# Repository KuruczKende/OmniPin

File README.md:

# OmniPin

## Description
This is a badge that can be customized while worn. The project contructs from a mobile application and a device.

### Technical Details
Microcontroller used: ESP32-C3-Mini-1
E-Paper: GDEM0154F51H

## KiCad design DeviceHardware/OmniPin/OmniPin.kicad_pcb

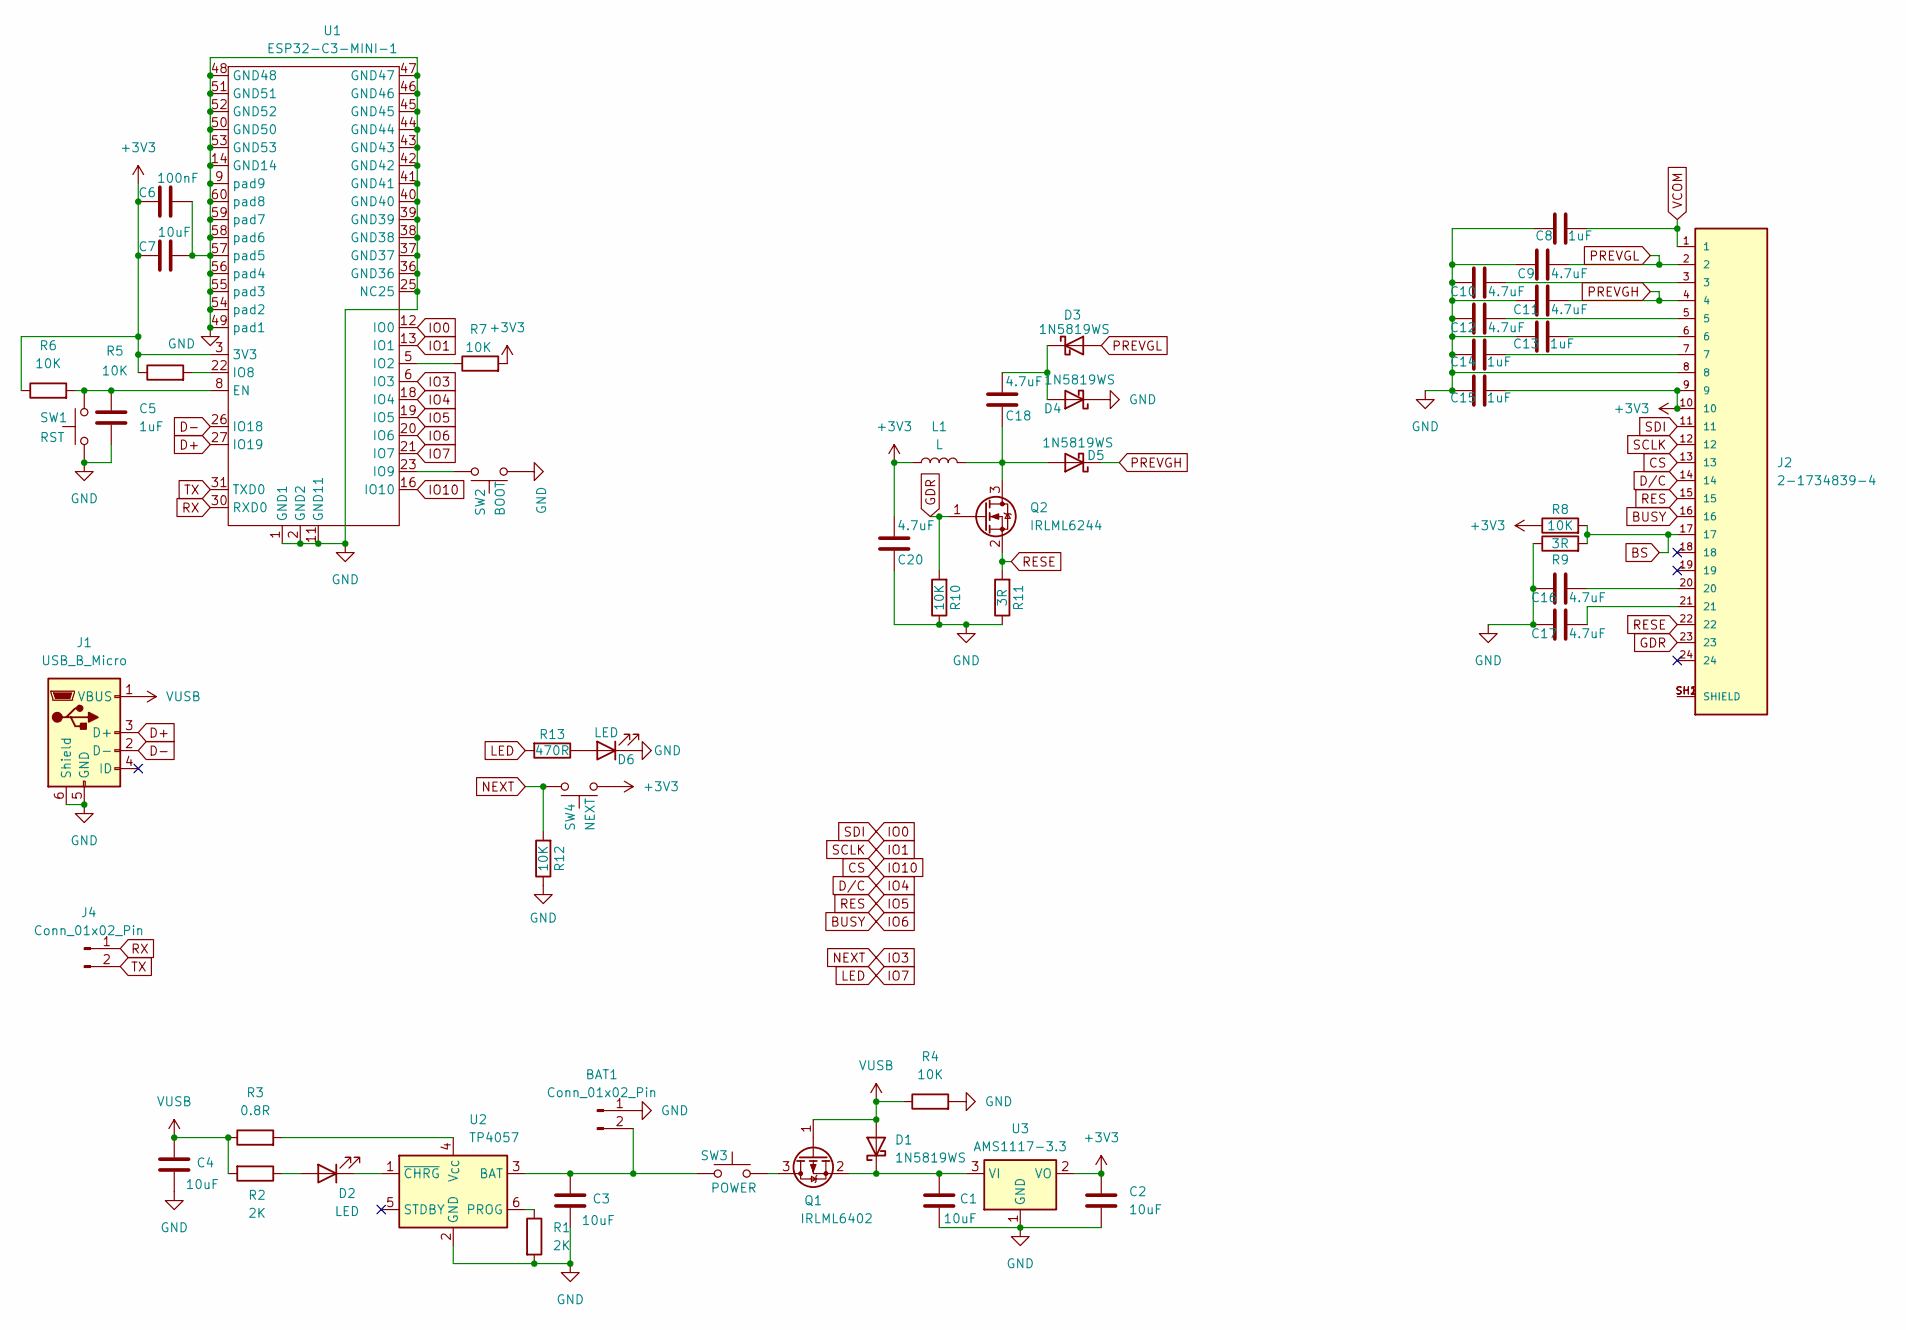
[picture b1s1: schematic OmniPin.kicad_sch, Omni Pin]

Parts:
BAT1: Conn_01x02_Pin; PinHeader_1x02_P1.27mm_Vertical
C1, C2, C3, C4, C7: 10uF; C_0603_1608Metric
C5, C8, C13, C14, C15: 1uF; C_0603_1608Metric
C6: 100nF; C_0603_1608Metric
C9, C10, C11, C12, C16, C17, C18, C20: 4.7uF; C_0603_1608Metric
D1, D3, D4, D5: 1N5819WS; D_SOD-323_HandSoldering
D2, D6: LED; LED_0603_1608Metric
J1: USB_B_Micro; USB_Micro-B_Amphenol_10118193-0002LF_Horizontal
J2: 2-1734839-4; TE_2-1734839-4; PARTREV 05-06
J4: Conn_01x02_Pin; PinHeader_1x02_P1.27mm_Vertical
L1: L; L_Taiyo-Yuden_NR-30xx_HandSoldering
Q1: IRLML6402; SOT-23
Q2: IRLML6244; SOT-23
R1, R2: 2K; R_0603_1608Metric
R3: 0.8R; R_0603_1608Metric
R4, R5, R6, R7, R8, R10, R12: 10K; R_0603_1608Metric
R9, R11: 3R; R_0603_1608Metric
R13: 470R; R_0603_1608Metric
SW1: RST; SW_SPST_B3U-3000P-B
SW2: BOOT; SolderJumper-2_P1.3mm_Open_RoundedPad1.0x1.5mm
SW3: POWER; PinHeader_1x02_P1.27mm_Vertical
SW4: NEXT; SW_SPST_B3U-3000P-B
U1: ESP32-C3-MINI-1
U2: TP4057; TSOT-23-6
U3: AMS1117-3.3; SOT-223-3_TabPin2

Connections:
+3V3: C2.1, C6.1, C7.1, C15.2, C20.1, J2.9, J2.10, L1.1, R5.1, R6.1, R7.2, R8.1, SW4.1, U1.3 (3V3), U3.2 (VO)
BS: J2.17, R8.2, R9.2
BUSY: J2.16, U1.20 (IO6)
CS: J2.13, U1.16 (IO10)
D+: J1.3 (D+), U1.27 (IO19)
D-: J1.2 (D-), U1.26 (IO18)
D/C: J2.14, U1.18 (IO4)
GDR: J2.23, Q2.1 (G), R10.2
GND: BAT1.1, C1.2, C2.2, C3.2, C4.2, C5.2, C6.2, C7.2, C8.1, C9.2, C10.2, C11.2, C12.2, C13.1, C14.1, C15.1, C16.2, C17.2, C20.2, D4.1 (K), D6.1 (K), J1.5 (GND), J1.6 (Shield), J2.8, R1.2, R4.2, R9.1, R10.1, R11.1, R12.1, SW1.1, SW2.1, U1.1 (GND1), U1.2 (GND2), U1.9 (pad9), U1.11 (GND11), U1.14 (GND14), U1.25 (NC25), U1.36 (GND36), U1.37 (GND37), U1.38 (GND38), U1.39 (GND39), U1.40 (GND40), U1.41 (GND41), U1.42 (GND42), U1.43 (GND43), U1.44 (GND44), U1.45 (GND45), U1.46 (GND46), U1.47 (GND47), U1.48 (GND48), U1.49 (pad1), U1.50 (GND50), U1.51 (GND51), U1.52 (GND52), U1.53 (GND53), U1.54 (pad2), U1.55 (pad3), U1.56 (pad4), U1.57 (pad5), U1.58 (pad6), U1.59 (pad7), U1.60 (pad8), U2.2 (GND), U3.1 (GND)
IO0: J2.11, U1.12 (IO0)
IO1: J2.12, U1.13 (IO1)
IO3: R12.2, SW4.2, U1.6 (IO3)
IO5: J2.15, U1.19 (IO5)
IO7: R13.2, U1.21 (IO7)
unnamed: BAT1.2, C3.1, SW3.1, U2.3 (BAT)
unnamed: C10.1, J2.3
unnamed: C12.1, J2.5
unnamed: C13.2, J2.6
unnamed: C14.2, J2.7
unnamed: C16.1, J2.20
unnamed: C17.1, J2.21
unnamed: C1.1, D1.1 (K), Q1.2 (S), U3.3 (VI)
unnamed: D2.2 (A), R2.1
unnamed: D2.1 (K), U2.1 (~CHRG)
unnamed: C18.1, D3.1 (K), D4.2 (A)
unnamed: C18.2, D5.2 (A), L1.2, Q2.3 (D)
unnamed: D6.2 (A), R13.1
unnamed: J2.SH1 (SHIELD), J2.SH2 (SHIELD)
unnamed: Q1.3 (D), SW3.2
unnamed: C5.1, R6.2, SW1.2, U1.8 (EN)
unnamed: R7.1, U1.5 (IO2)
unnamed: R5.2, U1.22 (IO8)
unnamed: SW2.2, U1.23 (IO9)
unnamed: R1.1, U2.6 (PROG)
unnamed: R3.2, U2.4 (V_{CC})
PREVGH: C11.1, D5.1 (K), J2.4
PREVGL: C9.1, D3.2 (A), J2.2
RESE: J2.22, Q2.2 (S), R11.2
RX: J4.1, U1.30 (RXD0)
TX: J4.2, U1.31 (TXD0)
VCOM: C8.2, J2.1
VUSB: C4.1, D1.2 (A), J1.1 (VBUS), Q1.1 (G), R2.2, R3.1, R4.1

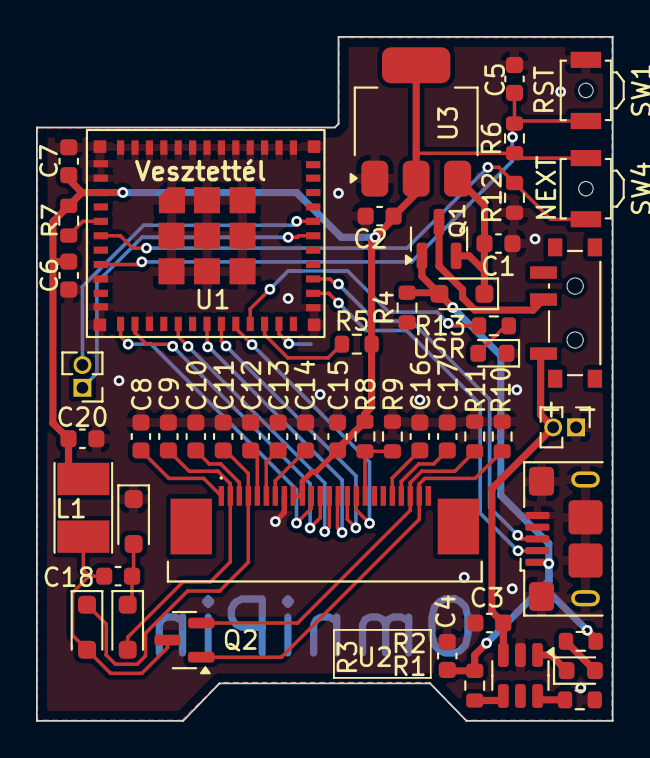
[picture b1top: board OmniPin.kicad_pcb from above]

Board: 2 copper layers, 32.0 x 38.0 mm, 56 parts (1 on the bottom side), 42 nets.

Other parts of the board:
T1, T1#2, T1#3, T1#4: Tab

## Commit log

2025-07-07 adding the device(hw+sw) to the repo
2025-07-08 update pcb
2025-10-02 hw panelization
